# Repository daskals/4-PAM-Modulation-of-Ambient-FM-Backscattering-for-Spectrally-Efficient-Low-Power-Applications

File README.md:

# 4-PAM Modulation of Ambient FM Backscattering for Spectrally Efficient Low Power Applications
Design files of  IEEE publication: 4-PAM Modulation of Ambient FM Backscattering
for Spectrally Efficient Low Power Applications

Ambient backscatter uses radio frequency signals
available in the environment (e.g. radio broadcasting, television or mobile telephony) to transmit data effectively leading
to significant energy and cost efficiency increase. This repo
presents a novel wireless tag, which for the first time utilizes
4-pulse amplitude modulation (4-PAM) technique to modulate
the ambient backscattered FM signals in order to send data to a
nearby low-cost software defined radio reader. The tag is based
on an RF front-end that uses a single transistor controlled by
an ultra low-power microcontroller. The microcontroller includes
an analog-to-digital converter (ADC) for sensing and a digital-to-analog converter (DAC) for RF front-end control. A proof-of-concept prototype is demonstrated in an indoor environment
with the low bit rate of 345 bps and power consumption 27 µW.
It operated using a real FM station at 34.5 Km away and the tag-to-reader distance was tested at 1 m. The value of energy spent
in this modulator was 78.2 nJ/bit at 345 bps and 27.7 nJ/bit at
10.2 Kbps.

**Authors:**

Spyridon Nektarios Daskalakis\
Ricardo Correia\
George Goussetis\
Manos M. Tentzeris\
Nuno Borges Carvalho\
Apostolos Georgiadis\

---
IEEE Xplore: https://ieeexplore.ieee.org/document/8534458/
Local: http://daskalakispiros.com/files/daskalakis_mtt_2018.pdf

---

---
**Questions/issues**
Inquiries regarding the scripts provided are cordially welcome.

---
**Citing**

If you use our design, please cite [[1]](https://ieeexplore.ieee.org/document/8534458/).

```bibtex
@article{daskalakis2018four,
  title={Four-PAM modulation of ambient FM backscattering for spectrally efficient low-power applications},
  author={Daskalakis, Spyridon Nektarios and Correia, Ricardo and Goussetis, George and Tentzeris, Manos M and Carvalho, Nuno Borges and Georgiadis, Apostolos},
  journal={IEEE Transactions on Microwave Theory and Techniques},
  volume={66},
  number={12},
  pages={5909--5921},
  year={2018},
  publisher={IEEE}
}
}
 
```

[[1]](https://ieeexplore.ieee.org/document/8534458) S. N. Daskalakis, R. Correia, G.Goussetis, M. M. Tentzeris, N. B. Carvalho and A. Georgiadis, 4-PAM Modulation of Ambient FM Backscattering for Spectrally Efficient Low Power Applications, IEEE Transactions on Microwave Theory and Techniques (TMTT), Vol. 66, No. 12, pp. 5909-5921, December 2018.

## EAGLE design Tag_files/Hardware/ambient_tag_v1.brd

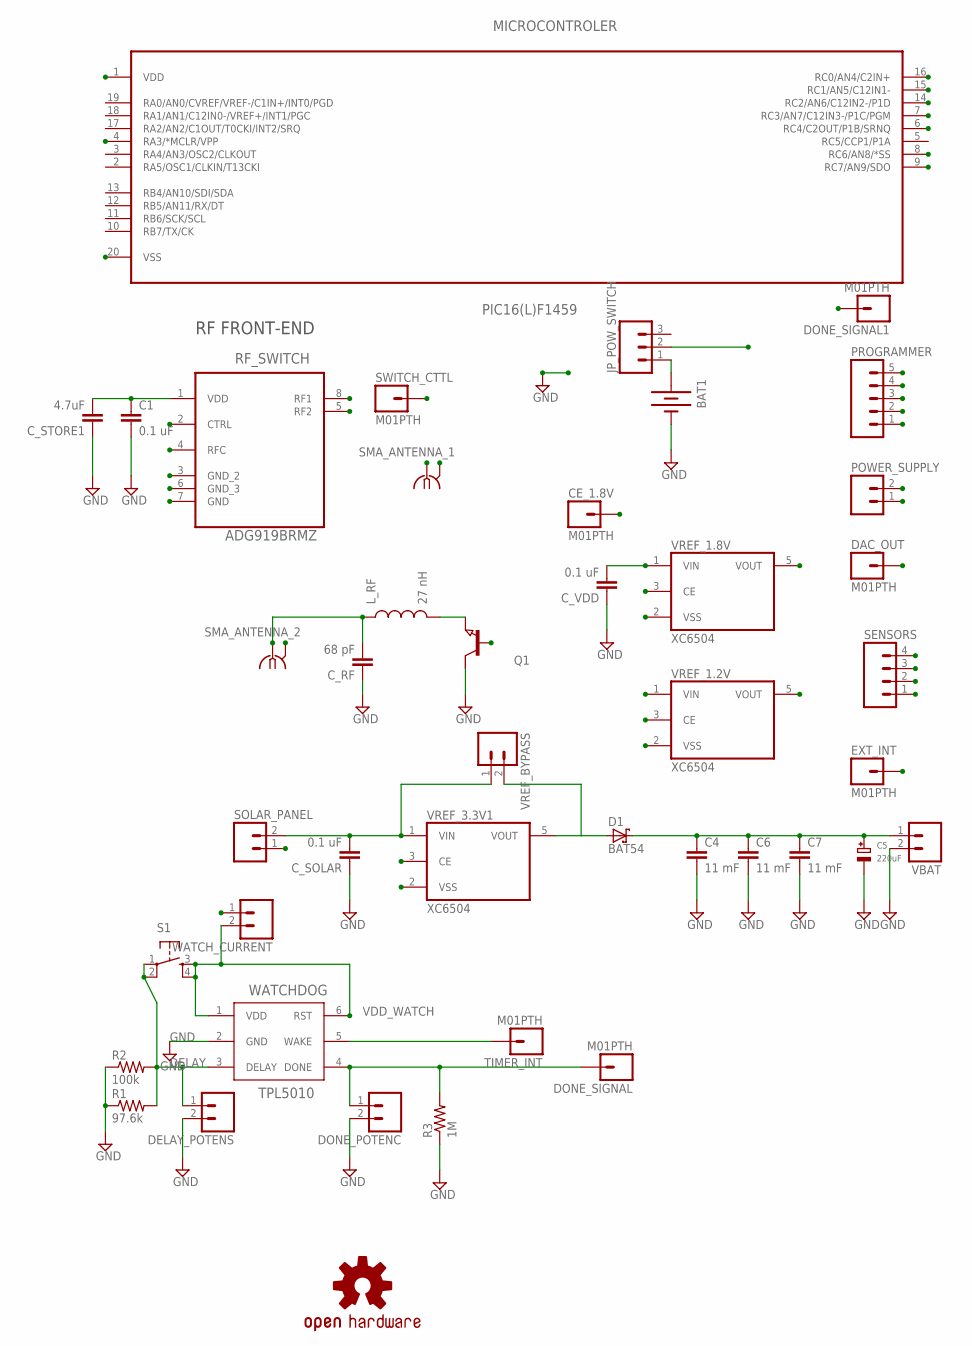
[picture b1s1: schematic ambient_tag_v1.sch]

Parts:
BAT1: BATTERY20PTH_LAB; BATTCOM_20MM_PTH
C1: 0.1 uF; 0603-CAP
C4, C6, C7: 11 mF; 1210
C5: 220uF; EIA7343-31/D-R
CE_1.8V: M01PTH; 1X01
C_RF: 68 pF; 0603-CAP
C_SOLAR: 0.1 uF; 0603-CAP
C_STORE1: 4.7uF; 0805
C_VDD: 0.1 uF; 0603-CAP
D1: BAT54; SOT23
DAC_OUT: M01PTH; 1X01
DELAY_POTENS: M02PTH; 1X02
DONE_POTENC: M02PTH; 1X02
DONE_SIGNAL, DONE_SIGNAL1: M01PTH; 1X01
EXT_INT: M01PTH; 1X01
JP_POW_SWITCH: M03LOCK; 1X03_LOCK
LOGO1: OSHW-LOGOL; OSHW-LOGO-L
L_RF: 27 nH; 0603
MICROCONTROLER: PIC16(L)F1459; SOP65P780X200-20N
POWER_SUPPLY: M02PTH; 1X02
PROGRAMMER: M05PTH; 1X05
Q1: NPN-TRANSISTIOR-2COLSOT89; SOT89
R1: 97.6k; R0805
R2: 100k; R0805
R3: 1M; R0805
RF_SWITCH: ADG919BRMZ; SOP65P490X110-8N
S1: TAC_SWITCHSMD; TACTILE_SWITCH_SMD
SENSORS: M04LOCK; 1X04_LOCK
SMA_ANTENNA_1, SMA_ANTENNA_2: SMA-142-0701-881/886; J502-ND-142-0701-881/886
SOLAR_PANEL: M02PTH; 1X02
SWITCH_CTTL: M01PTH; 1X01
TIMER_INT: M01PTH; 1X01
VBAT: M02PTH; 1X02
VREF_1.2V, VREF_1.8V, VREF_3.3V1: XC6504; SOT23-5
VREF_BYPASS: M02PTH; 1X02
WATCHDOG: TPL5010; TSOT-23
WATCH_CURRENT: M02PTH; 1X02

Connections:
CE: CE_1.8V.1, VREF_1.8V.3 (CE)
DAC1: DAC_OUT.1, MICROCONTROLER.14 (RC2/AN6/C12IN2-/P1D), Q1.1 (B)
DELAY: DELAY_POTENS.1, R1.2, R2.2, S1.1, S1.2, WATCHDOG.3 (DELAY)
DONE: DONE_POTENC.1, DONE_SIGNAL.1, R3.2, WATCHDOG.4 (DONE)
DONE_OUT: DONE_SIGNAL1.1, MICROCONTROLER.7 (RC3/AN7/C12IN3-/P1C/PGM)
GND: BAT1.2 (-), C1.2, C4.2, C5.-, C6.2, C7.2, C_RF.1, C_SOLAR.1, C_STORE1.1, C_VDD.1, DELAY_POTENS.2, DONE_POTENC.2, MICROCONTROLER.20 (VSS), POWER_SUPPLY.1, PROGRAMMER.3, Q1.2 (C), R1.1, R2.1, R3.1, RF_SWITCH.3 (GND_2), RF_SWITCH.6 (GND_3), RF_SWITCH.7 (GND), SENSORS.1, SENSORS.3, SMA_ANTENNA_2.G@1 (2), SMA_ANTENNA_2.G@2 (2), SMA_ANTENNA_2.G@3 (2), SMA_ANTENNA_2.G@4 (2), SOLAR_PANEL.1, VBAT.2, VREF_1.2V.2 (VSS), VREF_1.8V.2 (VSS), VREF_3.3V1.2 (VSS), WATCHDOG.2 (GND)
MCLR: MICROCONTROLER.4 (RA3/*MCLR/VPP), PROGRAMMER.5
unnamed: L_RF.2, Q1.3 (E)
unnamed: TIMER_INT.1, WATCHDOG.5 (WAKE)
unnamed: D1.1 (A), VREF_3.3V1.5 (VOUT), VREF_BYPASS.2
unnamed: BAT1.1 (+), JP_POW_SWITCH.1
RF1: RF_SWITCH.8 (RF1)
RF2: RF_SWITCH.5 (RF2), SMA_ANTENNA_1.G@1 (2), SMA_ANTENNA_1.G@2 (2), SMA_ANTENNA_1.G@3 (2), SMA_ANTENNA_1.G@4 (2)
RFC: RF_SWITCH.4 (RFC), SMA_ANTENNA_1.1
SENSOR1: MICROCONTROLER.8 (RC6/AN8/*SS), SENSORS.4
SENSOR2: MICROCONTROLER.9 (RC7/AN9/SDO), SENSORS.2
SOLAR: C_SOLAR.2, SOLAR_PANEL.2, VREF_3.3V1.1 (VIN), VREF_3.3V1.3 (CE), VREF_BYPASS.1
SPCLK: EXT_INT.1, MICROCONTROLER.15 (RC1/AN5/C12IN1-), PROGRAMMER.1
SPDAT: MICROCONTROLER.16 (RC0/AN4/C2IN+), PROGRAMMER.2, VREF_1.2V.5 (VOUT)
SWITCH_CTTL: MICROCONTROLER.6 (RC4/C2OUT/P1B/SRNQ), RF_SWITCH.2 (CTRL), SWITCH_CTTL.1
TRANSISTOR_OUT: C_RF.2, L_RF.1, SMA_ANTENNA_2.1
VDD: C4.1, C5.+, C6.1, C7.1, C_VDD.2, D1.3 (C), JP_POW_SWITCH.2, VBAT.1, VREF_1.8V.1 (VIN), WATCH_CURRENT.1
VDD_1.8V: C1.1, C_STORE1.2, MICROCONTROLER.1 (VDD), POWER_SUPPLY.2, PROGRAMMER.4, RF_SWITCH.1 (VDD), VREF_1.2V.1 (VIN), VREF_1.2V.3 (CE), VREF_1.8V.5 (VOUT)
VDD_WATCH: S1.3, S1.4, WATCHDOG.1 (VDD), WATCHDOG.6 (RST), WATCH_CURRENT.2

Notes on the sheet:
RF FRONT-END

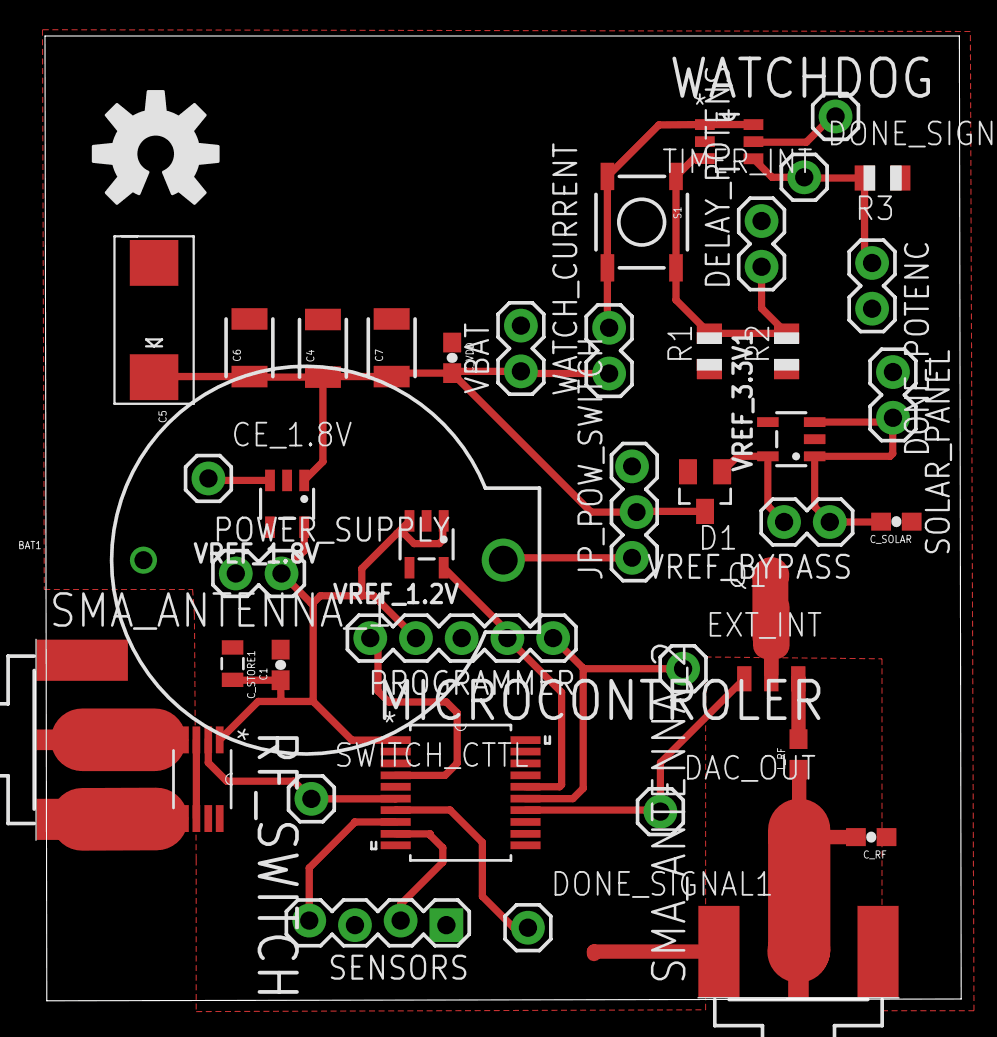
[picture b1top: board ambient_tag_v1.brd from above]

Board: 2 copper layers, 51.4 x 53.6 mm, 43 parts (0 on the bottom side), 23 nets.

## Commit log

2021-10-15 Update files 2
2021-10-15 Update 2
2021-10-15 Update 4

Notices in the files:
parts and their libraries:
semipassiveTag_library: Licensing: CC v3.0 Share-Alike You are welcome to use this library for commercial purposes.
SparkFun-Aesthetics: Licensing: Creative Commons ShareAlike 4.0 International - https://creativecommons.org/licenses/by-sa/4.0
torex: Copyright (C) 2015, Bob Starr
